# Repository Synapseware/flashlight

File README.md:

flashlight
==========

## about
Uses 2xAA batteries powering an LTC3490 constant current LED driver.  This LED driver is an efficient, compact design and relatively easy to setup.

## board
* Dimensions are 15mm x 25 mm
  * LED is normal 2 lead type, white, mounted on the trace side
* Center of LED is about center of the board, so 12.5mm in
* Constant-current circuit is an [LTC3490](http://www.linear.com/product/LTC3490).

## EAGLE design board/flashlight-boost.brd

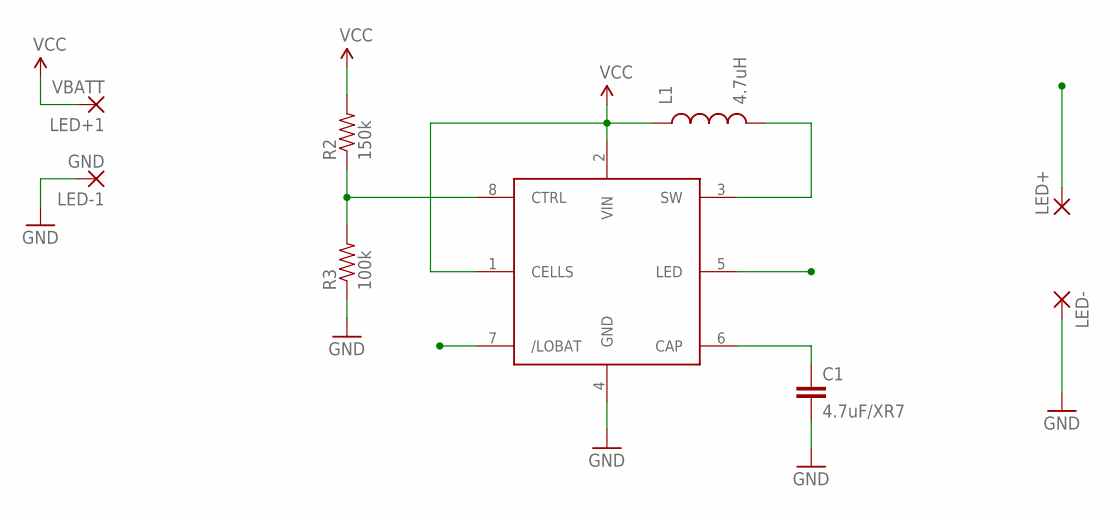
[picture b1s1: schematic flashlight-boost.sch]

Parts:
C1: 4.7uF/XR7; 1206
L1: 4.7uH; 1210
LED+: 2,54/1,0
LED+1: VBATT; 2,54/1,0
LED-: 2,54/1,0
LED-1: GND; 2,54/1,0
R2: 150k; 0603-RES
R3: 100k; 0603-RES
U$1: LTC3490NSOIC-8; NSOIC-8

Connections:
GND: C1.2, LED-.1, LED-1.1, R3.1, U$1.4 (GND)
LED: LED+.1, U$1.5 (LED)
unnamed: L1.2, U$1.3 (SW)
unnamed: C1.1, U$1.6 (CAP)
unnamed: R2.1, R3.2, U$1.8 (CTRL)
VCC: L1.1, LED+1.1, R2.2, U$1.1 (CELLS), U$1.2 (VIN)

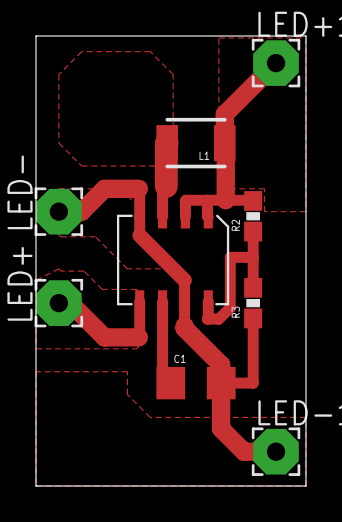
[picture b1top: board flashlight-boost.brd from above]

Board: 2 copper layers, 15.0 x 25.0 mm, 9 parts (0 on the bottom side), 6 nets.

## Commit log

2014-07-27 Adding new flashlight project - board layout
2014-07-27 Adding git ignore file to exclude Eagle temporary files
2014-07-27 Cleaning up files and updating readme
2014-07-27 Adding photos of old board
2014-07-27 removing constant current LED driver since the current sense resistor for it is the same value as the LED series resistor
2014-07-29 misc updates
2014-08-02 Converting driver board to use LTC3490 part
2014-08-16 Final board layout
2015-07-24 Fixing voltage divider.
    The voltage divider was setup to yield a control voltage of 0.6v which for a 2.4v input sets up the LED driver for a driver current of just over 25mA. The drive current should be between 80mA and 100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

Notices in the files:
parts and their libraries:
SparkFun-Passives: Licensing: CC v3.0 Share-Alike You are welcome to use this library for commercial purposes.
